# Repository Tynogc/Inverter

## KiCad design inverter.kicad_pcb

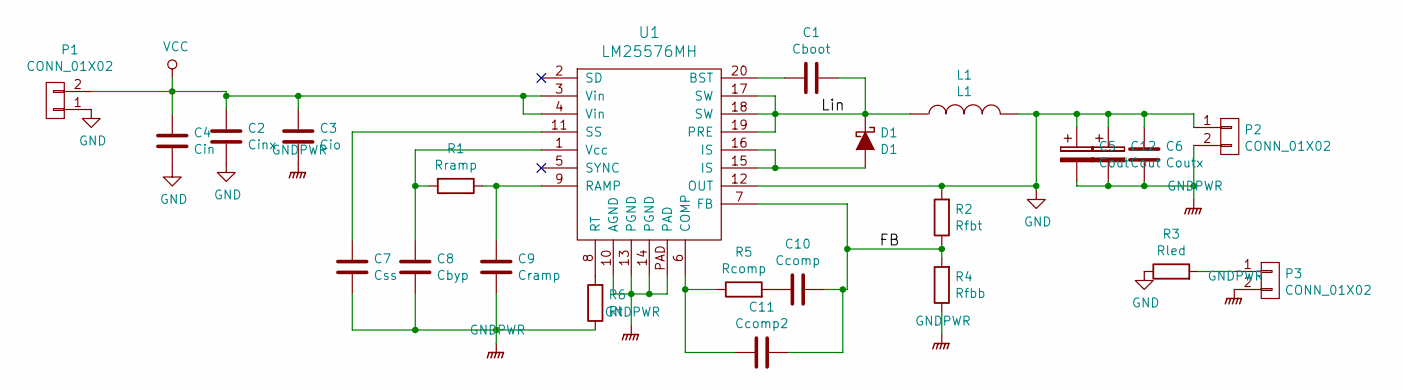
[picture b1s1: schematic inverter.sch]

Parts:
C1: Cboot; C_0603
C2: Cinx; C_0603
C3: Cio; C_0805
C4: Cin; C_0805
C5, C12: Cout; TantalC_SizeB_EIA-3528_Reflow
C6: Coutx; C_0805
C7: Css; C_0603
C8: Cbyp; C_0603
C9: Cramp; C_0805
C10: Ccomp; C_0603
C11: Ccomp2; C_0805
D1: D1; SMA_Standard
L1: L1; SELF1408
P1, P2: CONN_01X02; Screw_Connector_5,08mm_x2
P3: CONN_01X02; Pin_Header_Straight_1x02
R1: Rramp; R_0805
R2: Rfbt; R_0805
R3: Rled; R_0805
R4: Rfbb; R_0805
R5: Rcomp; R_0805
R6: Rt; R_0805
U1: LM25576MH; TSSOP-20_4.4x6.5mm_Pitch0.65mm_EP

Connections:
/FB: C10.2, C11.2, R2.1, R4.2, U1.7 (FB)
/Lin: C1.1, D1.1 (K), L1.1, U1.17 (SW), U1.18 (SW), U1.19 (PRE)
GND: C2.2, C4.2, C5.1, C6.2, C12.1, L1.2, P1.1, P2.1, R2.2, R3.1, U1.12 (OUT)
GNDPWR: C3.2, C5.2, C6.1, C7.2, C8.2, C9.2, C12.2, P2.2, P3.2, R4.1, R6.1, U1.10 (AGND), U1.13 (PGND), U1.14 (PGND), U1.PAD
unnamed: C1.2, U1.20 (BST)
unnamed: C7.1, U1.11 (SS)
unnamed: C8.1, R1.2, U1.1 (Vcc)
unnamed: C9.1, R1.1, U1.9 (RAMP)
unnamed: C10.1, R5.2
unnamed: C11.1, R5.1, U1.6 (COMP)
unnamed: D1.2 (A), U1.15 (IS), U1.16 (IS)
unnamed: P3.1, R3.2
unnamed: R6.2, U1.8 (RT)
VCC: C2.1, C3.1, C4.1, P1.2, U1.3 (Vin), U1.4 (Vin)

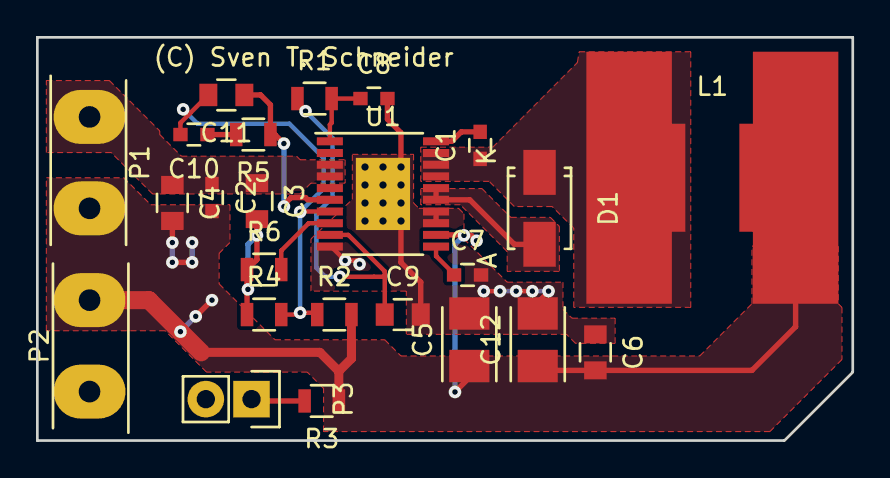
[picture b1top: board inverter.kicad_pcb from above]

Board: 2 copper layers, 45.3 x 22.4 mm, 24 parts (0 on the bottom side), 14 nets.

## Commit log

2016-02-02 Inital commit
2016-02-05 Fertig gestellt
